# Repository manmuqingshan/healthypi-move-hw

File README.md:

<div align="center">

</div>

# HealthyPi Move Hardware Repository

**An open-source biometric monitor in a watch form factor**

HealthyPi Move is a revolutionary open-source wearable device that provides clinical-grade biometric monitoring in a sleek watch form factor. Designed with the principles of data ownership, repairability, and customization at its core, HealthyPi Move offers comprehensive health tracking capabilities without the limitations of proprietary systems.

## Project Status

** Successfully Funded & Shipping!** - HealthyPi Move reached 329% of its funding goal on Crowd Supply and is now shipping to backers worldwide.

- **Campaign Status**: Funded and In Stock
- **Availability**: Shipping now - [Order on Crowd Supply](https://www.crowdsupply.com/protocentral/healthypi-move)
- **Price**: $299 USD

## Key Features

### Comprehensive Biometric Monitoring
- **ECG (Electrocardiogram)**: Single-lead ECG for heart rhythm analysis
- **Dual PPG Sensors**: Wrist and finger-based photoplethysmography
- **SpO₂ Monitoring**: Blood oxygen saturation measurement
- **Blood Pressure Trending**: Cuffless BP monitoring via finger sensor
- **EDA/GSR**: Galvanic skin response for stress monitoring
- **Heart Rate Variability (HRV)**: Advanced cardiac health metrics
- **Respiration Rate**: ECG-derived breathing pattern analysis
- **Body Temperature**: Contact-based temperature sensing
- **Activity Tracking**: 6-axis IMU for motion and activity monitoring

### Technical Specifications
- **Processor**: Nordic nRF5340 dual-core ARM Cortex-M33 SoC
- **Memory**: 512 KB RAM, 128 MB QSPI flash storage
- **Display**: 1.2" round AMOLED (390×390 pixels) with capacitive touch
- **Battery**: 300 mAh Li-Po with 5-day typical usage life
- **Connectivity**: Bluetooth Low Energy 6.0, USB Type-C
- **Charging**: USB Type-C with Power Delivery support
- **Dimensions**: 43mm diameter × 13mm thickness
- **Strap Compatibility**: Standard 22mm watch straps

### Open Source Advantages
- **Own Your Data**: No cloud dependency, all data stored locally
- **User Programmable**: Based on Zephyr RTOS and nRF Connect SDK
- **Repairable Design**: Modular components, no glue assembly
- **Custom Applications**: Full access to develop your own algorithms
- **OTA Updates**: Over-the-air firmware updates via BLE or USB

## Repository Contents

### Hardware Design Files
* **`/pcbs/main board/`** - Main board PCB designs (KiCad and Eagle formats)
  * Latest: `kicad_pc_healthypi_move_nRF5340_v12/` (KiCad)
  * Legacy versions: v1-v5 (Eagle format)
* **`/pcbs/sensor board/`** - Sensor board PCB designs
  * Latest: `kicad_pc_healthypi_move_sensor_v9/`
* **`/pcbs/finger sensor board/`** - Finger sensor PCB designs
  * Latest: `pc_healthypi_move_sensor_connector_v4/`
* **`/pcbs/bottom board/`** - Bottom board PCB designs
  * Latest: `pc_healthypi_move_bottom_pcb_v4/`
* **`/enclosure/`** - 3D printable and injection-molded enclosure designs
  * **`/enclosure/fusion/`** - Autodesk Fusion 360 source files
  * **`/enclosure/stls/`** - 3D printable STL files
* **`/docs/`** - Documentation and images

## Related Repositories

- **[HealthyPi Move Firmware](https://github.com/Protocentral/healthypi-move-fw)** - Zephyr RTOS-based firmware
- **[HealthyPi Move Mobile App](https://github.com/Protocentral/healthypi_move_flutter/)** - Flutter-based companion app (Android/iOS)

## Sensor Details

### ECG (Electrocardiogram)
- **IC**: MAX30001 ECG and bio-impedance front-end
- **Configuration**: Single-lead ECG (Lead-II equivalent)
- **Electrodes**: Back electrode (wrist contact) + top bezel electrode (finger contact)
- **Sampling Rate**: Up to 512 Hz
- **Features**: Real-time heart rate, HRV calculation, respiration rate derivation

### PPG (Photoplethysmography) - Dual Configuration
#### Wrist PPG Sensor
- **IC**: MAX86141 with MAX32664C biometric sensor hub
- **LEDs**: 2× Green, 1× Red, 1× Infrared
- **Photodiodes**: 2× photodiodes for improved signal quality
- **Use Cases**: Continuous HR monitoring, SpO₂ measurement

#### Finger PPG Sensor (Optional)
- **IC**: MAX30101 with MAX32664D biometric sensor hub
- **LEDs**: Red and Infrared
- **Use Cases**: High-accuracy SpO₂, blood pressure trending, pulse transit time
- **Connection**: USB Type-C port with custom connector board

### Additional Sensors
- **IMU**: BMI323 6-DoF (accelerometer + gyroscope)
- **Temperature**: MAX30208 body temperature sensor
- **EDA/GSR**: Custom electrodes for galvanic skin response

## Enclosure Design

The HealthyPi Move features a thoughtfully designed enclosure that prioritizes repairability and modularity:

### Key Design Principles
- **Screw Assembly**: No glue used - completely serviceable
- **Modular Construction**: Separate main board, sensor board, and battery modules
- **Standard Straps**: Compatible with any 22mm watch strap
- **Material**: Biocompatible ABS-type injection-molded plastic

### Chassis System
- **4-Screw Design**: Easy access to internal components
- **Component Protection**: Isolated battery compartment for safety
- **Display Replacement**: User-replaceable AMOLED display
- **Sensor Access**: Removable sensor boards for upgrades/repairs

## Applications & Use Cases

### Personal Health Monitoring
- **Continuous Monitoring**: 24/7 heart rate, activity, and sleep tracking
- **Stress Management**: Real-time EDA/GSR feedback for stress awareness
- **Cardiovascular Health**: ECG recording and HRV analysis
- **Fitness Tracking**: Advanced metrics beyond basic step counting

### Research & Development
- **Clinical Research**: IRB-approved studies with institutional oversight
- **Algorithm Development**: Platform for custom biometric algorithms
- **Data Collection**: High-resolution, multi-modal biometric datasets
- **Educational Use**: Teaching platform for biomedical engineering

### Healthcare Applications*
- **Remote Monitoring**: Patient monitoring with healthcare provider integration
- **Chronic Disease Management**: Long-term tracking for conditions like AFib
- **Telehealth Integration**: Data export for virtual consultations
- **Clinical Trials**: Research-grade data collection platform

*_Requires appropriate regulatory approvals (FDA, CE, etc.) for medical use_

## 🛠️ Development Environment

### Firmware Development
- **OS**: Zephyr RTOS with nRF Connect SDK
- **Language**: C/C++
- **IDE**: VS Code with nRF Connect extension
- **Debugging**: SWD via USB Type-C DAM
- **OTA Updates**: BLE and USB DFU support

### Mobile App Development
- **Framework**: Flutter (Dart)
- **Platforms**: Android, iOS, macOS, Windows, Linux
- **Communication**: Bluetooth Low Energy
- **Data Format**: JSON, CSV, PDF export capabilities

### Hardware Customization
- **PCB Design**: KiCad (latest versions) and Eagle (legacy)
- **Enclosure**: Autodesk Fusion 360 source files
- **3D Printing**: STL files provided for rapid prototyping
- **Manufacturing**: Gerber files and assembly documentation included

## 📚 Documentation & Support

Visit our [Documentation Site](https://move.protocentral.com/) for detailed guides.

## ⚖️ Regulatory Information

### Important Disclaimers
⚠️ **Medical Device Notice**: HealthyPi Move is **NOT** a certified medical device. It is designed for:
- Consumer wellness and fitness tracking
- Research and educational applications
- Development of medical devices (with proper certification)

## 📄 License Information

This project is open source and licensed under multiple licenses depending on the component:

### Hardware
**All hardware designs are released under the [CERN-OHL-P v2](https://ohwr.org/cern_ohl_p_v2.txt)** license.

Copyright CERN 2020. This source describes Open Hardware and is licensed under the CERN-OHL-P v2. You may redistribute and modify this documentation and make products using it under the terms of the CERN-OHL-P v2 (https://cern.ch/cern-ohl). This documentation is distributed WITHOUT ANY EXPRESS OR IMPLIED WARRANTY, INCLUDING OF MERCHANTABILITY, SATISFACTORY QUALITY AND FITNESS FOR A PARTICULAR PURPOSE.

### Software
**All software is released under the [MIT License](http://opensource.org/licenses/MIT).**

THE SOFTWARE IS PROVIDED "AS IS", WITHOUT WARRANTY OF ANY KIND, EXPRESS OR IMPLIED, INCLUDING BUT NOT LIMITED TO THE WARRANTIES OF MERCHANTABILITY, FITNESS FOR A PARTICULAR PURPOSE AND NONINFRINGEMENT. IN NO EVENT SHALL THE AUTHORS OR COPYRIGHT HOLDERS BE LIABLE FOR ANY CLAIM, DAMAGES OR OTHER LIABILITY, WHETHER IN AN ACTION OF CONTRACT, TORT OR OTHERWISE, ARISING FROM, OUT OF OR IN CONNECTION WITH THE SOFTWARE OR THE USE OR OTHER DEALINGS IN THE SOFTWARE.

### Documentation
**All documentation is released under [Creative Commons Share-alike 4.0 International](http://creativecommons.org/licenses/by-sa/4.0/).**

You are free to:
- **Share** — copy and redistribute the material in any medium or format
- **Adapt** — remix, transform, and build upon the material for any purpose, even commercially

Under the following terms:
- **Attribution** — You must give appropriate credit, provide a link to the license, and indicate if changes were made
- **ShareAlike** — If you remix, transform, or build upon the material, you must distribute your contributions under the same license as the original

Please check [*LICENSE.md*](LICENSE.md) for detailed license descriptions.

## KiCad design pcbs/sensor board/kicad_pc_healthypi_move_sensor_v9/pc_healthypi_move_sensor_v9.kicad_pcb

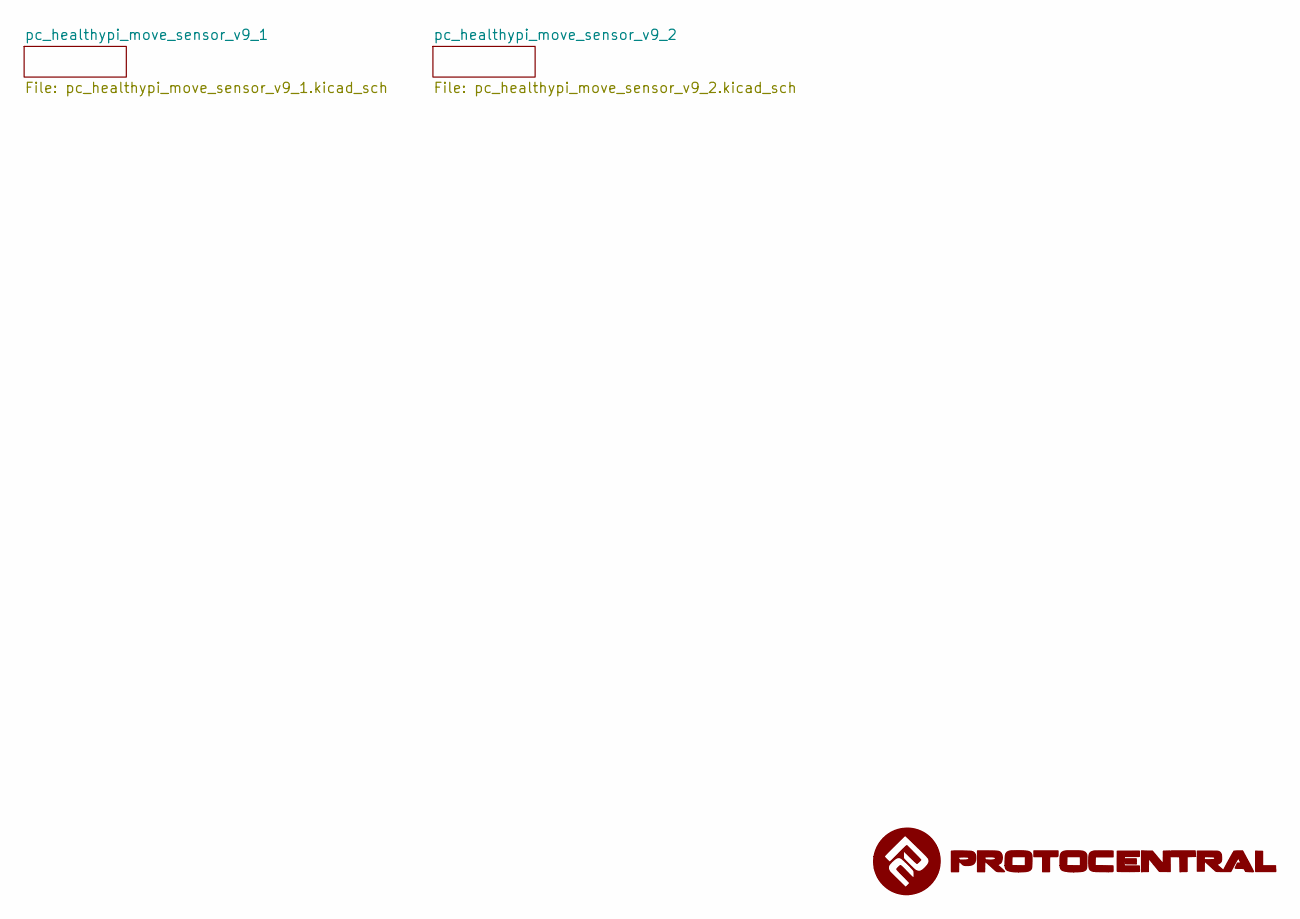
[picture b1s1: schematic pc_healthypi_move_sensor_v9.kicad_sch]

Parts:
U8: (no value)

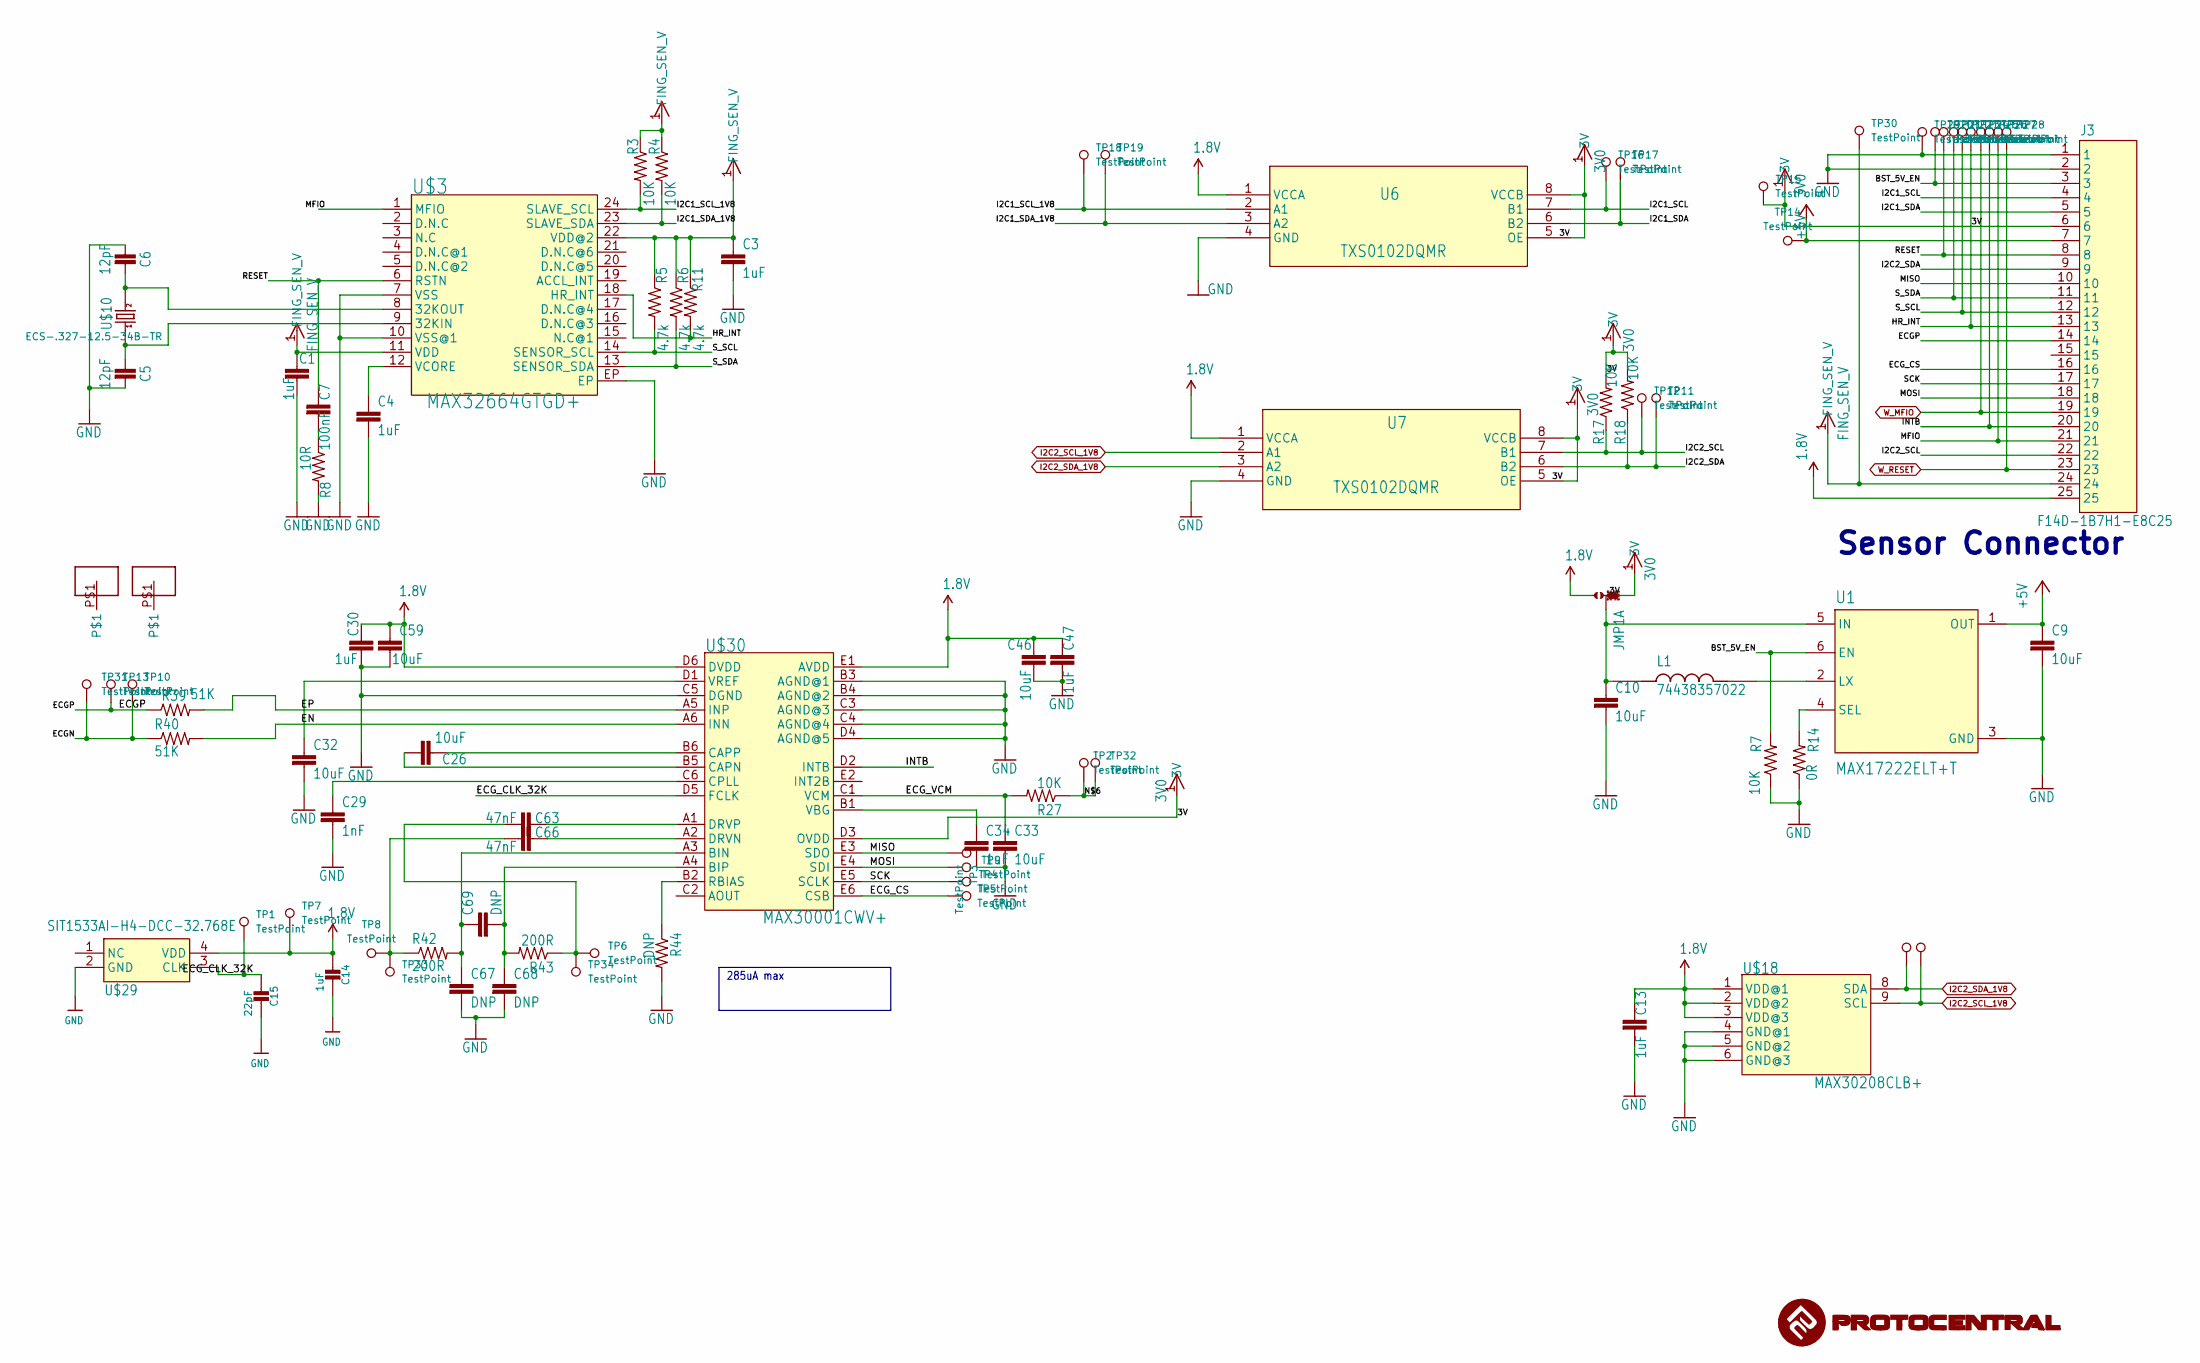
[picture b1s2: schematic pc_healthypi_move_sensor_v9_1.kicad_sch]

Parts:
C1, C3, C4, C13, C30, C34, C47: 1uF; C0402
C5, C6: 12pF; C0402
C7: 100nF; C0402
C9, C10, C26, C32, C33, C46, C59: 10uF; C0402
C14: 1uF; 0402
C15: 22pF; 0402
C29: 1nF; C0402
C63, C66: 47nF; C0402
C67, C68, C69: DNP; C0402
J3: F14D-1B7H1-E8C25; AMPHENOL_F14D-1B7H1-E8C25_38825256
JMP1: 0R-JUMPA; SolderJumper-3_P1.3mm_Bridged2Bar12_Pad1.0x1.5mm
L1: 74438357022; L_Coilcraft_XxL4020
R3, R4: 10K; 0402-RES
R5, R6, R11: 4.7k; 0402-RES
R7, R17, R18, R27: 10K; R_0402_1005Metric
R8: 10R; 0402-RES
R14: 0R; R_0402_1005Metric
R39, R40: 51K; 0402-RES
R42, R43: 200R; 0402-RES
R44: DNP; 0402-RES
SWIO8, SWIO9: TPTP11R; TestPoint_Pad_1.0x1.0mm
TP1, TP2, TP3, TP4, TP5, TP6, TP7, TP8, TP9, TP10, TP11, TP12, TP13, TP14, TP15, TP16, TP17, TP18, TP19, TP20, TP21, TP22, TP23, TP24, TP25, TP26, TP27, TP28, TP29, TP30: TestPoint; TestPoint_Pad_1.0x1.0mm
TP31, TP32, TP33, TP34: TestPoint; TestPoint_THTPad_D2.0mm_Drill1.0mm
U1: MAX17222ELT+T; SON65P200X200X80-6N
U6, U7: TXS0102DQMR; IC_TXS0102DQMR
U9: (no value)
U$3: MAX32664GTGD+; MAX-QFN24
U$5, U$28: SPACER
U$10: ECS-.327-12.5-34B-TR; ECX-31B
U$18: MAX30208CLB+; IC_MAX30208CLB_
U$29: SIT1533AI-H4-DCC-32.768E; SIT1533
U$30: MAX30001CWV+; BGA30N50P5X6_274X292X69N

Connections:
1.8V: C13.1, C14.1, C30.1, C46.1, C47.1, C59.1, J3.25, JMP1.3, TP7.1, U6.1 (VCCA), U7.1 (VCCA), U$18.1 (VDD@1), U$18.2 (VDD@2), U$18.3 (VDD@3), U$29.4 (VDD), U$30.D6 (DVDD), U$30.E1 (AVDD); also elsewhere on the board
3V0: J3.6, J3.13, JMP1.1, R11.2, R17.2, R18.2, TP15.1, TP24.1, U6.5 (OE), U6.8 (VCCB), U7.5 (OE), U7.8 (VCCB), U$3.18 (HR_INT), U$30.D3 (OVDD)
+5V: C9.1, J3.7, TP14.1, U1.1 (OUT); also elsewhere on the board
/pc_healthypi_move_sensor_v7_1/BST_5V_EN: J3.3, R7.2, TP20.1, U1.6 (EN)
/pc_healthypi_move_sensor_v7_1/ECGN: R40.1, TP10.1, TP31.1
/pc_healthypi_move_sensor_v7_1/ECGP: J3.14, R39.1, TP13.1
/pc_healthypi_move_sensor_v7_1/ECG_CLK_32K: C15.1, TP1.1, U$29.3 (CLK), U$30.D5 (FCLK)
/pc_healthypi_move_sensor_v7_1/ECG_CS: J3.16, TP5.1, U$30.E6 (CSB)
/pc_healthypi_move_sensor_v7_1/ECG_VCM: C33.1, R27.2, U$30.C1 (VCM)
/pc_healthypi_move_sensor_v7_1/EN: R40.2, U$30.A6 (INN)
/pc_healthypi_move_sensor_v7_1/EP: R39.2, U$30.A5 (INP)
/pc_healthypi_move_sensor_v7_1/I2C1_SCL: J3.4, TP16.1, U6.7 (B1)
/pc_healthypi_move_sensor_v7_1/I2C1_SCL_1V8: R3.2, TP18.1, U6.2 (A1), U$3.24 (SLAVE_SCL)
/pc_healthypi_move_sensor_v7_1/I2C1_SDA: J3.5, TP17.1, U6.6 (B2)
/pc_healthypi_move_sensor_v7_1/I2C1_SDA_1V8: R4.2, TP19.1, U6.3 (A2), U$3.23 (SLAVE_SDA)
/pc_healthypi_move_sensor_v7_1/I2C2_SCL: J3.22, R17.1, TP12.1, U7.7 (B1)
/pc_healthypi_move_sensor_v7_1/I2C2_SDA: J3.9, R18.1, TP11.1, U7.6 (B2)
/pc_healthypi_move_sensor_v7_1/INTB: J3.20, TP26.1, U$30.D2 (INTB)
/pc_healthypi_move_sensor_v7_1/MFIO: J3.21, TP27.1, U$3.1 (MFIO)
/pc_healthypi_move_sensor_v7_1/MISO: J3.10, TP3.1, U$30.E3 (SDO)
/pc_healthypi_move_sensor_v7_1/MOSI: J3.18, TP9.1, U$30.E4 (SDI)
/pc_healthypi_move_sensor_v7_1/N$6: R27.1, TP2.1, TP32.1
/pc_healthypi_move_sensor_v7_1/RESET: C7.1, J3.8, TP21.1, U$3.6 (RSTN)
/pc_healthypi_move_sensor_v7_1/SCK: J3.17, TP4.1, U$30.E5 (SCLK)
/pc_healthypi_move_sensor_v7_1/S_SCL: J3.12, R5.2, TP23.1, U$3.14 (SENSOR_SCL)
/pc_healthypi_move_sensor_v7_1/S_SDA: J3.11, R6.2, TP22.1, U$3.13 (SENSOR_SDA)
FING_SEN_V: C1.1, C3.1, J3.24, R3.1, R4.1, R5.1, R6.1, R11.1, TP30.1, U$3.11 (VDD), U$3.22 (VDD@2)
GND: C1.2, C3.2, C4.2, C5.2, C6.1, C9.2, C10.2, C13.2, C14.2, C15.2, C29.2, C30.2, C32.2, C33.2, C34.2, C46.2, C47.2, C59.2, C67.2, C68.2, J3.1, J3.2, R7.1, R8.2, R14.1, R44.2, TP29.1, U1.3 (GND), U6.4 (GND), U7.4 (GND), U$3.7 (VSS), U$3.10 (VSS@1), U$3.EP, U$18.4 (GND@1), U$18.5 (GND@2), U$18.6 (GND@3), U$29.2 (GND), U$30.B3 (AGND@1), U$30.B4 (AGND@2), U$30.C3 (AGND@3), U$30.C4 (AGND@4), U$30.C5 (DGND), U$30.D4 (AGND@5); also elsewhere on the board
I2C2_SCL_1V8: SWIO9.1, U7.2 (A1), U$18.9 (SCL); also elsewhere on the board
I2C2_SDA_1V8: SWIO8.1, U7.3 (A2), U$18.8 (SDA); also elsewhere on the board
unnamed: C7.2, R8.1
unnamed: C63.1, R43.1, TP6.1, TP34.1
unnamed: C66.1, R42.1, TP8.1, TP33.1
unnamed: C10.1, JMP1.2, L1.1, U1.5 (IN)
unnamed: L1.2, U1.2 (LX)
unnamed: R14.2, U1.4 (SEL)
unnamed: C4.1, U$3.12 (VCORE)
unnamed: C5.1, U$3.9 (32KIN), U$10.P$1 (1)
unnamed: C6.2, U$3.8 (32KOUT), U$10.P$2 (2)
unnamed: C67.1, C69.1, R42.2, U$30.A3 (BIN)
unnamed: C68.1, C69.2, R43.2, U$30.A4 (BIP)
unnamed: C26.2, U$30.B5 (CAPN)
unnamed: C26.1, U$30.B6 (CAPP)
unnamed: C29.1, U$30.C6 (CPLL)
unnamed: C66.2, U$30.A2 (DRVN)
unnamed: C63.2, U$30.A1 (DRVP)
unnamed: R44.1, U$30.B2 (RBIAS)
unnamed: C34.1, U$30.B1 (VBG)
unnamed: C32.1, U$30.D1 (VREF)
W_MFIO: J3.19, TP25.1; also elsewhere on the board
W_RESET: J3.23, TP28.1; also elsewhere on the board

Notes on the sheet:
Sensor Connector
285uA max

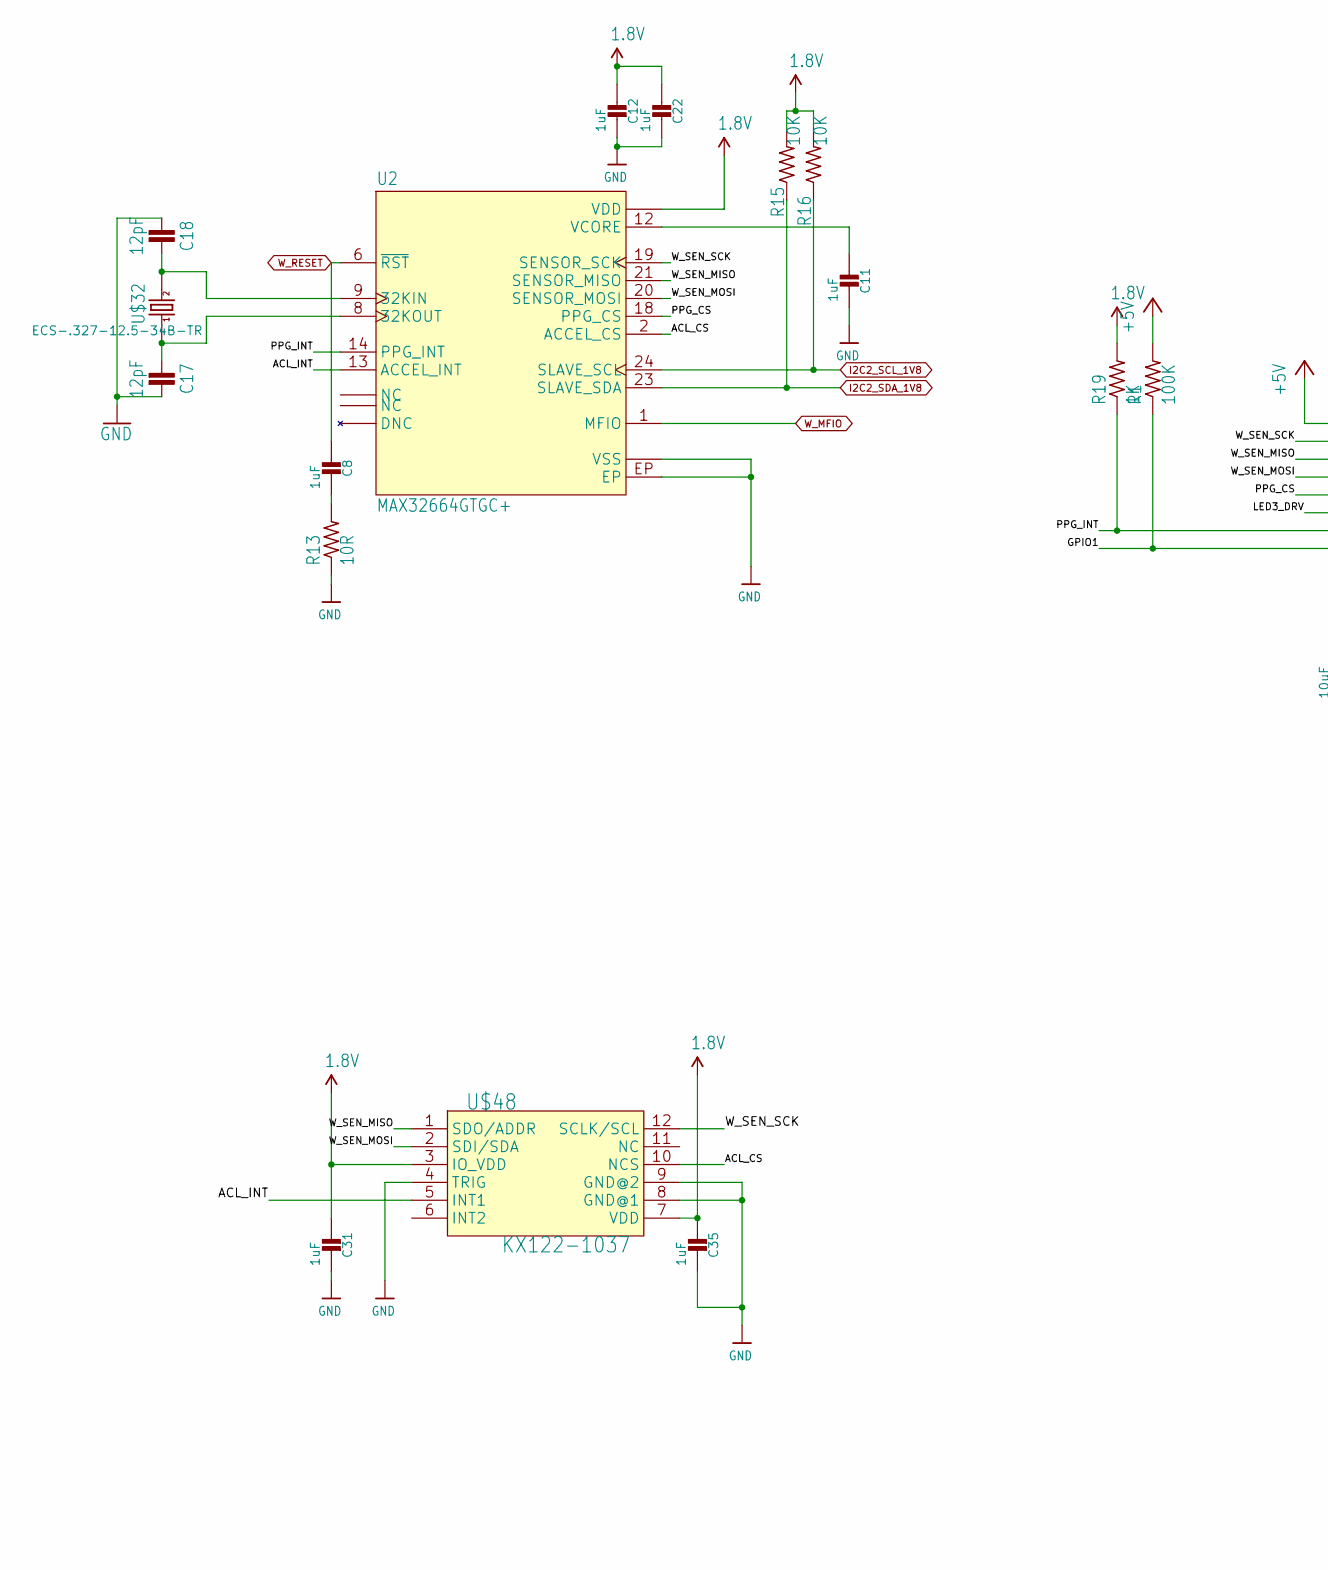
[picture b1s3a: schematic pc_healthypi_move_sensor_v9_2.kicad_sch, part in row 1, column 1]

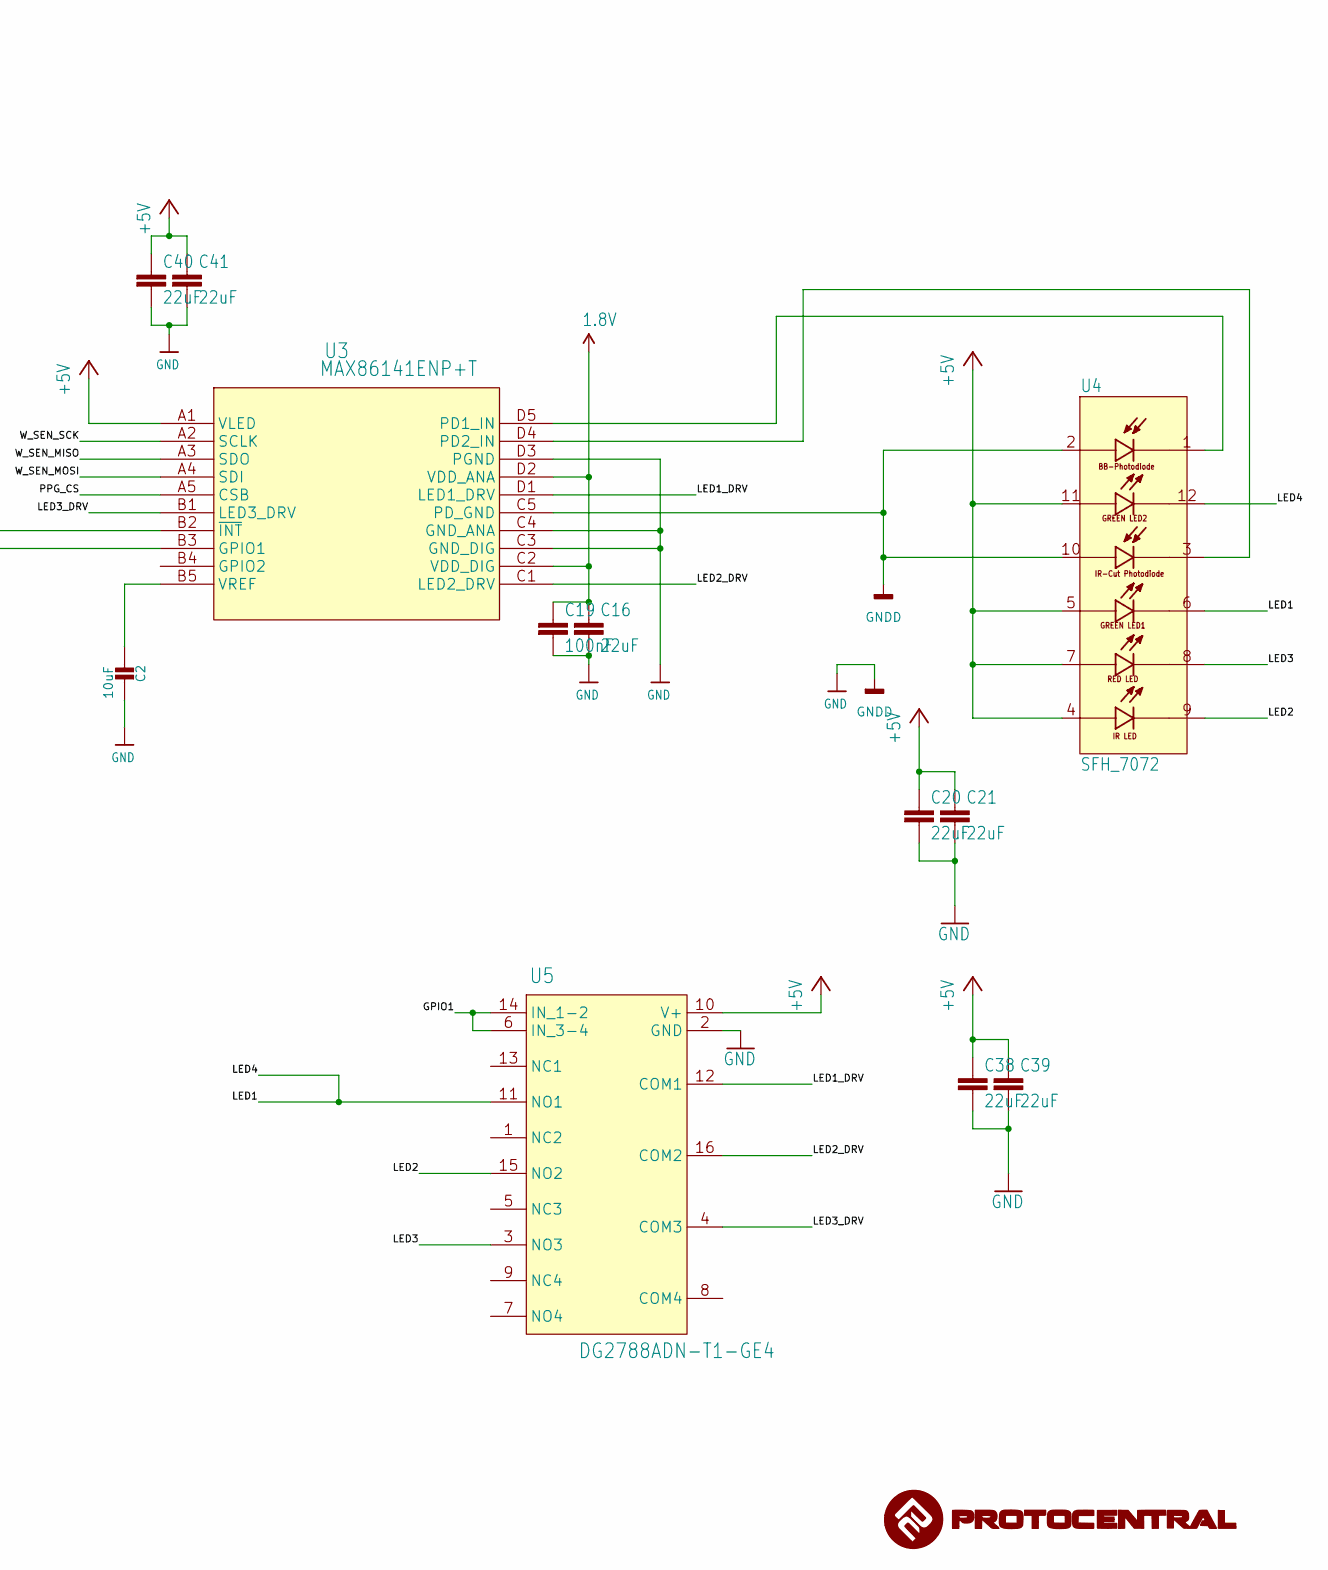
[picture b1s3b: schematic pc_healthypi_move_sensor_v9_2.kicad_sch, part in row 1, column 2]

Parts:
C2: 10uF; 0402
C8, C11, C12, C22, C31, C35: 1uF; 0402
C16, C20, C21, C38, C39, C40, C41: 22uF; C0402
C17, C18: 12pF; C0402
C19: 100nF; C0402
R1: 100K; R_0402_1005Metric
R13: 10R; R_0402_1005Metric
R15, R16: 10K; R_0402_1005Metric
R19: 1K; R_0402_1005Metric
U2: MAX32664GTGC+; MAX-QFN24
U3: MAX86141ENP+T; 21-100134_N201A2-1_MXM
U4: SFH_7072; XDCR_SFH_7072
U5: DG2788ADN-T1-GE4; MINIQFN-16_VIS
U10: (no value)
U$32: ECS-.327-12.5-34B-TR; ECX-31B
U$48: KX122-1037; KIONIX_KXTJ3-1057

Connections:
1.8V: C12.1, C16.1, C19.1, C22.1, C31.1, C35.1, R15.2, R16.2, R19.2, U2.11 (VDD), U2.22 (VDD), U3.C2 (VDD_DIG), U3.D2 (VDD_ANA), U$48.3 (IO_VDD), U$48.7 (VDD); also elsewhere on the board
+5V: C20.1, C21.1, C38.1, C39.1, C40.1, C41.1, R1.2, U3.A1 (VLED), U4.4 (IA), U4.5 (G1A), U4.7 (RA), U4.11 (G2A), U5.10 (V+); also elsewhere on the board
/pc_healthypi_move_sensor_v7_2/ACL_CS: U2.2 (ACCEL_CS), U$48.10 (NCS)
/pc_healthypi_move_sensor_v7_2/ACL_INT: U2.13 (ACCEL_INT), U$48.5 (INT1)
/pc_healthypi_move_sensor_v7_2/GPIO1: R1.1, U3.B3 (GPIO1), U5.6 (IN_3-4), U5.14 (IN_1-2)
/pc_healthypi_move_sensor_v7_2/LED1: U4.6 (G1C), U4.12 (G2C), U5.11 (NO1)
/pc_healthypi_move_sensor_v7_2/LED1_DRV: U3.D1 (LED1_DRV), U5.12 (COM1)
/pc_healthypi_move_sensor_v7_2/LED2: U4.9 (IC), U5.15 (NO2)
/pc_healthypi_move_sensor_v7_2/LED2_DRV: U3.C1 (LED2_DRV), U5.16 (COM2)
/pc_healthypi_move_sensor_v7_2/LED3: U4.8 (RC), U5.3 (NO3)
/pc_healthypi_move_sensor_v7_2/LED3_DRV: U3.B1 (LED3_DRV), U5.4 (COM3)
/pc_healthypi_move_sensor_v7_2/PPG_CS: U2.18 (PPG_CS), U3.A5 (CSB)
/pc_healthypi_move_sensor_v7_2/PPG_INT: R19.1, U2.14 (PPG_INT), U3.B2 (~INT)
/pc_healthypi_move_sensor_v7_2/W_SEN_MISO: U2.21 (SENSOR_MISO), U3.A3 (SDO), U$48.1 (SDO/ADDR)
/pc_healthypi_move_sensor_v7_2/W_SEN_MOSI: U2.20 (SENSOR_MOSI), U3.A4 (SDI), U$48.2 (SDI/SDA)
/pc_healthypi_move_sensor_v7_2/W_SEN_SCK: U2.19 (SENSOR_SCK), U3.A2 (SCLK), U$48.12 (SCLK/SCL)
GND: C2.2, C11.2, C12.2, C16.2, C17.2, C18.1, C19.2, C20.2, C21.2, C22.2, C31.2, C35.2, C38.2, C39.2, C40.2, C41.2, R13.1, U2.7 (VSS), U2.10 (VSS), U2.EP, U3.C3 (GND_DIG), U3.C4 (GND_ANA), U3.C5 (PD_GND), U3.D3 (PGND), U4.2 (BPA), U4.10 (IPA), U5.2 (GND), U$48.4 (TRIG), U$48.8 (GND@1), U$48.9 (GND@2); also elsewhere on the board
I2C2_SCL_1V8: R16.1, U2.24 (SLAVE_SCL); also elsewhere on the board
I2C2_SDA_1V8: R15.1, U2.23 (SLAVE_SDA); also elsewhere on the board
unnamed: C2.1, U3.B5 (VREF)
unnamed: C8.2, R13.2
unnamed: C11.1, U2.12 (VCORE)
unnamed: U3.D5 (PD1_IN), U4.1 (BPC)
unnamed: U3.D4 (PD2_IN), U4.3 (IPC)
unnamed: C17.1, U2.8 (32KOUT), U$32.P$1 (1)
unnamed: C18.2, U2.9 (32KIN), U$32.P$2 (2)
W_MFIO: U2.1 (MFIO); also elsewhere on the board
W_RESET: C8.1, U2.6 (~RST); also elsewhere on the board

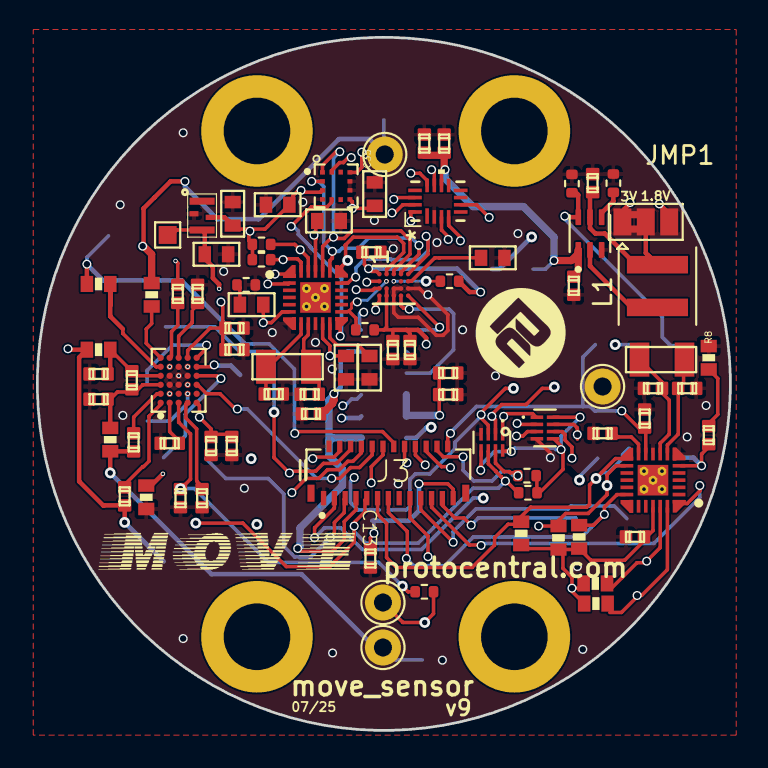
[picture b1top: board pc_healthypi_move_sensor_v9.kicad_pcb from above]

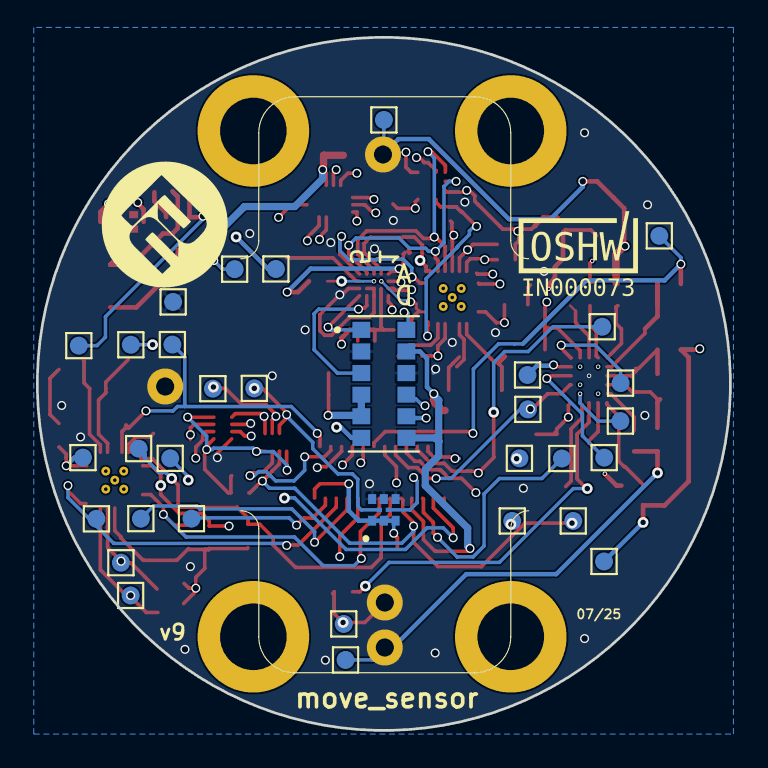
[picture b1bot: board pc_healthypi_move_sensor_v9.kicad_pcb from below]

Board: 6 copper layers, 38.5 x 38.5 mm, 121 parts (33 on the bottom side), 72 nets.

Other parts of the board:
U$6: HEALTHYPI_MOVE_LOGO_1_38825256
U$20, U$21: SPACER_38825256

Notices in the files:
README.md:
CC-BY-SA-4.0
